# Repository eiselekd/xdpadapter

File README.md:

# xdpadapter

Minnowboard.org adapter board for connecting to JTAG pins

## BOM

 * 4 bit 3.3V->1.8V level shifter http://www.ti.com/product/SN74LV4T125
   http://www.digikey.com/product-detail/en/texas-instruments/SN74LV4T125RGYR/296-40546-1-ND/5178423
   http://www.ti.com/lit/ds/symlink/sn74lv1t125.pdf
 * 1 bit 1.8V->3.3V level shifter http://www.ti.com/product/SN74LV1T125
   http://www.digikey.com/product-detail/en/texas-instruments/SN74LV1T125DCKR/296-37173-1-ND/4555590
   http://www.ti.com/lit/ds/symlink/sn74lv4t125.pdf
 * Connector Minnowboard: http://www.digikey.com/product-detail/en/3-5177986-2/A99215CT-ND/1894032
 * 20 pin ARM header: http://www.digikey.com/product-detail/en/samtec-inc/HTST-110-01-L-D/SAM8812-ND/2664195
 * Zener Diode 3.9V: http://www.digikey.com/product-detail/en/on-semiconductor/1SMA5915BT3G/1SMA5915BT3GOSCT-ND/1967012

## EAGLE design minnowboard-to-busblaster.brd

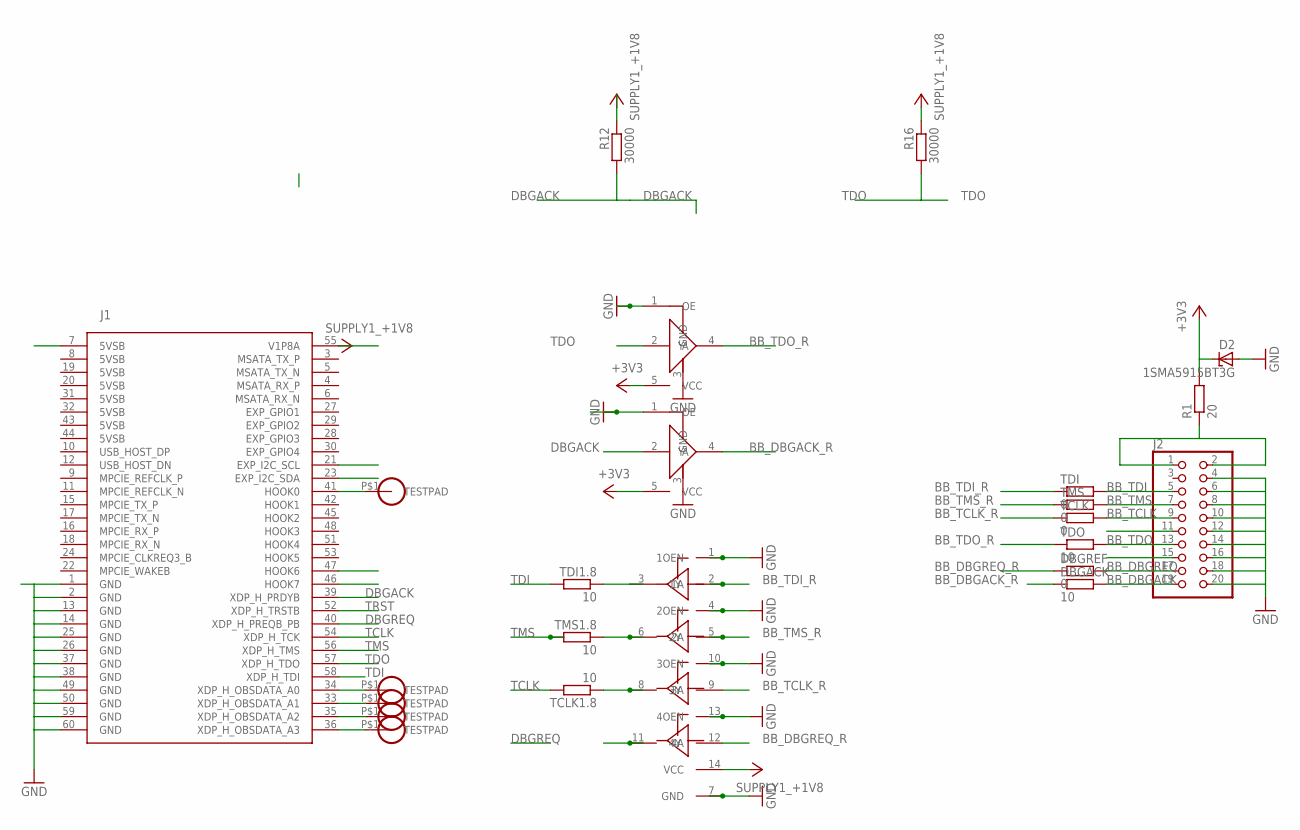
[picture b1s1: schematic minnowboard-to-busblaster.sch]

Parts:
A0, A1, A2, A3: TESTPAD
D2: 1SMA5915BT3G; DIODE_SMB
DBGACK: 10; R0805
DBGREF: 0; R0805
J1: CIRCUITCO_MINNOW2_HIGH_SPEED; CIRCUITCO_5177986-2
J2: LPC1768BOARD_PINHEAD_-_COPY_PINHD-2X10SHROUDED; LPC1768BOARD_PINHEAD_-_COPY_PINSHRD_PTH_2X10
R1: 20; R0805
R12, R16: 30000; R0805
TCLK: 0; R0805
TCLK1.8: 10; R0805
TDI: 0; R0805
TDI1.8: 10; R0805
TDO: 10; R0805
TMS: 0; R0805
TMS1.8: 10; R0805
U1: SN74LV4T125; PVQFN-N14
U2, U3: SN74LV1T125; SC70-5
U$1: TESTPAD

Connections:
+1V8: J1.55 (V1P8A), R12.1, R16.1, U1.14 (VCC)
+3V3: D2.C, R1.2, U2.5 (VCC), U3.5 (VCC)
BB_DBGACK: DBGACK.2, J2.19
BB_DBGACK_R: DBGACK.1, U2.4 (Y)
BB_DBGREQ: DBGREF.2, J2.17
BB_DBGREQ_R: DBGREF.1, U1.12 (4A)
BB_TCLK: J2.9, TCLK.2
BB_TCLK_R: TCLK.1, U1.9 (3A)
BB_TDI: J2.5, TDI.2
BB_TDI_R: TDI.1, U1.2 (1A)
BB_TDO: J2.13, TDO.2
BB_TDO_R: TDO.1, U3.4 (Y)
BB_TMS: J2.7, TMS.2
BB_TMS_R: TMS.1, U1.5 (2A)
DBGACK: J1.39 (XDP_H_PRDYB), R12.2, U2.2 (A)
DBGREQ: J1.40 (XDP_H_PREQB_PB)
GND: D2.A, J1.1 (GND), J1.2 (GND), J1.13 (GND), J1.14 (GND), J1.25 (GND), J1.26 (GND), J1.37 (GND), J1.38 (GND), J1.49 (GND), J1.50 (GND), J1.59 (GND), J1.60 (GND), J2.4, J2.18, J2.20, U1.1 (1OEN), U1.4 (2OEN), U1.7 (GND), U1.10 (3OEN), U1.13 (4OEN), U2.1 (OE), U2.3 (GND), U3.1 (OE), U3.3 (GND)
unnamed: J2.1, J2.2, R1.1
unnamed: TMS1.8.1, U1.6 (2Y)
unnamed: TDI1.8.1, U1.3 (1Y)
unnamed: TCLK1.8.1, U1.8 (3Y)
unnamed: A2.P$1, J1.35 (XDP_H_OBSDATA_A2)
unnamed: A0.P$1, J1.34 (XDP_H_OBSDATA_A0)
unnamed: A1.P$1, J1.33 (XDP_H_OBSDATA_A1)
unnamed: A3.P$1, J1.36 (XDP_H_OBSDATA_A3)
RMRST: J1.41 (HOOK0), U$1.P$1
TCLK: J1.54 (XDP_H_TCK), TCLK1.8.2
TDI: J1.58 (XDP_H_TDI), TDI1.8.2
TDO: J1.57 (XDP_H_TDO), R16.2, U3.2 (A)
TMS: J1.56 (XDP_H_TMS), TMS1.8.2
TRST: J1.52 (XDP_H_TRSTB)

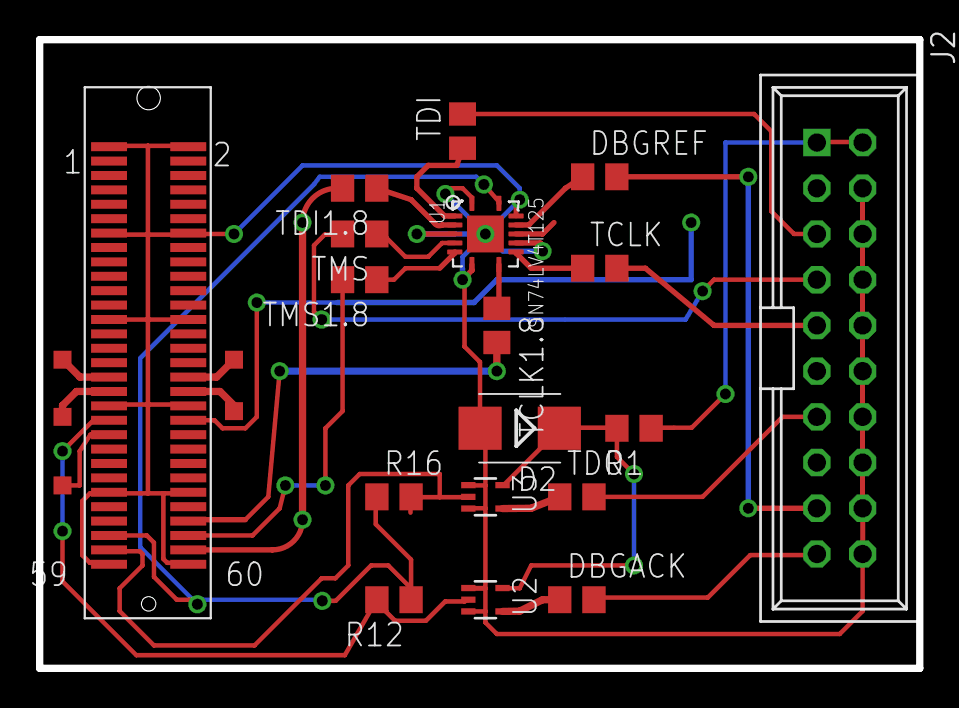
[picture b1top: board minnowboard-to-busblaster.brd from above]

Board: 2 copper layers, 48.9 x 34.9 mm, 23 parts (0 on the bottom side), 29 nets.
